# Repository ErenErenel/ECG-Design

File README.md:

# ECG Instrumentation & Heart Rate Variability Analysis

An analog ECG front-end (instrumentation amplifier + filtering) built around the
**OP484** quad op-amp, together with a Python analysis of the acquired signal for
beat-by-beat heart rate and heart rate variability (HRV).

Developed for the **EE 495 ECG Lab** at Northwestern University.

## Analog Front-End

A Lead-I ECG is acquired with RA and LA as the differential inputs and RL as the
right-leg reference ground. The signal chain runs on a single OP484 (four op-amps,
±5 V supply):

- **Instrumentation amplifier (3 op-amps)** — total gain ≈ 25
  - First stage (differential): G₁ = (2R₂ + R₁)/R₁ = 5, with R₂ = 20 kΩ, R₁ = 10 kΩ
  - Second stage (difference amp): G₂ = R₆/R₄ = 5, with R₆ = 100 kΩ, R₄ = 20 kΩ
- **Gain + filtering stage (4th op-amp)** — additional gain and approximate
  1–100 Hz band-limiting (high-pass + low-pass) to suppress baseline drift and
  high-frequency interference.

Bench verification with a 10 mV differential sine drove an output near 0.25 V,
confirming the ×25 instrumentation-amp gain across the 1–1000 Hz range.

## Heart Rate & HRV Analysis

A ~1-minute Lead-I recording was digitized at **fₛ = 1000 Hz** and analyzed in Python:

- **R-peak detection** — threshold-based (750 mV) with a 0.25 s refractory period and
  recovery of missed beats from abnormally long RR intervals. **72 R-peaks** detected.
- **Beat-by-beat heart rate** — computed from RR intervals (HRᵢ = 60 / RRᵢ),
  starting around 74.6 bpm.
- **HRV spectral analysis** — the mean HR is removed and an FFT-based power spectrum
  of the HR signal shows most variability at low frequencies (≤ 2 Hz, with a bump near
  ~0.18 Hz) associated with autonomic / respiratory modulation.

## Repository Structure

```
ECG-Design/
├── ECG PCB Files/          KiCad schematic, layout, and project for the ECG board
│   ├── ECG.kicad_sch
│   ├── ECG.kicad_pcb
│   └── ECG.kicad_pro
├── EE495 ECG Lab.pdf       Lab report: instrumentation amp design + ECG acquisition
└── Heart Rate Variability Analysis.pdf
                            HR and HRV analysis of the recorded ECG
```

Open `ECG PCB Files/ECG.kicad_pro` in **KiCad 7+** to view the schematic and board.

## License

Released under the [MIT License](LICENSE).

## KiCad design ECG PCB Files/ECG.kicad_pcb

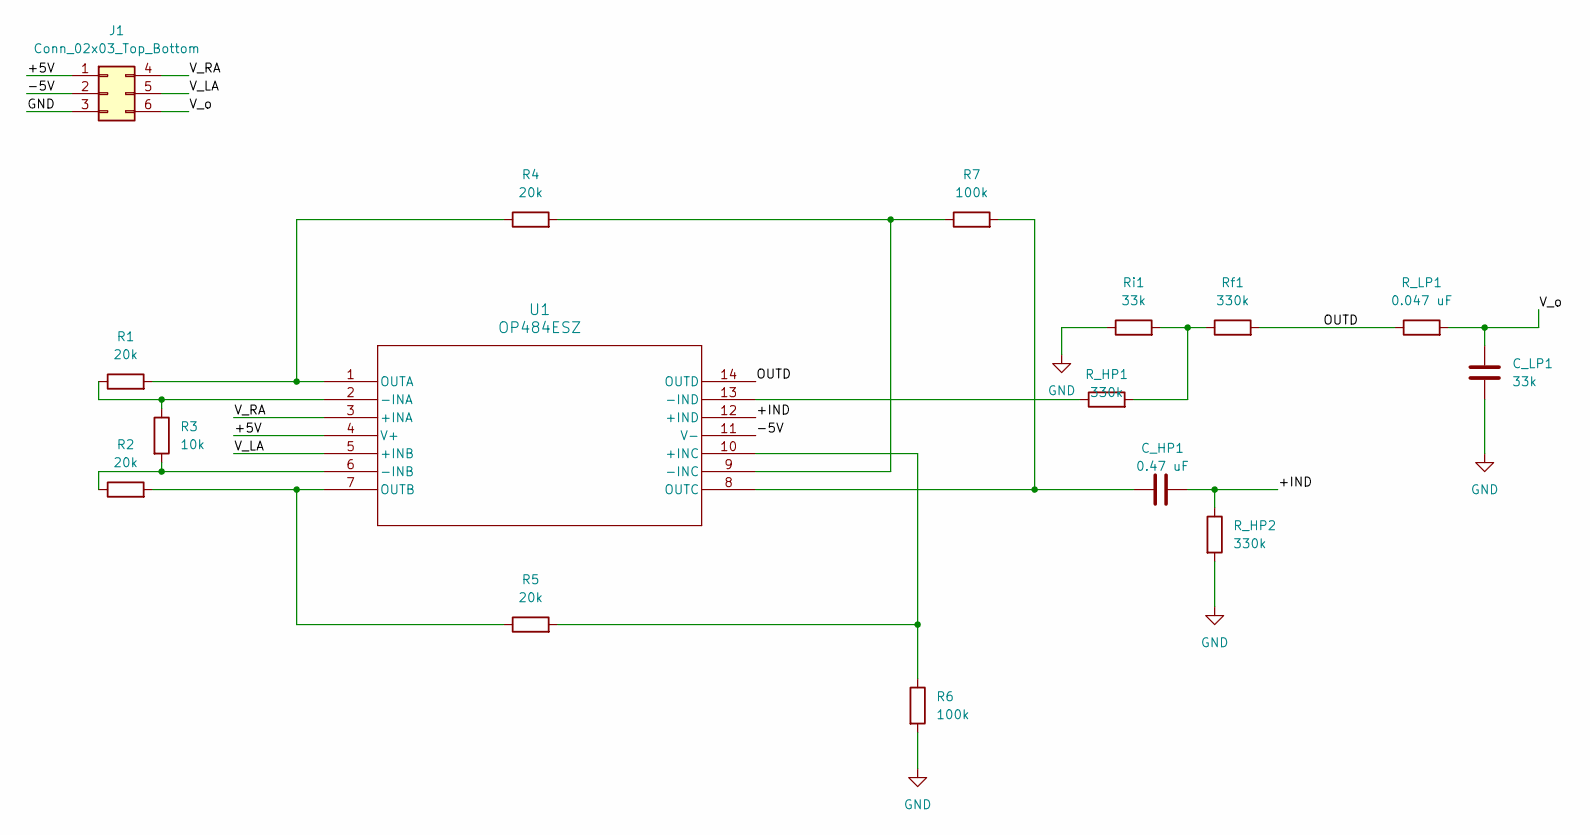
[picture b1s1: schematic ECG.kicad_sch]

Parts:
C_HP1: 0.47 uF; C_0805_2012Metric
C_LP1: 33k; C_0805_2012Metric
J1: Conn_02x03_Top_Bottom; PinHeader_2x03_P2.54mm_Vertical
R1, R2, R4, R5: 20k; R_0805_2012Metric
R3: 10k; R_0805_2012Metric
R6, R7: 100k; R_0805_2012Metric
R_HP1, R_HP2: 330k; R_0805_2012Metric
R_LP1: 0.047 uF; R_0805_2012Metric
Rf1: 330k; R_0805_2012Metric
Ri1: 33k; R_0805_2012Metric
U1: OP484ESZ; R_14_ADI

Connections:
/+5V: J1.1, U1.4 (V+)
/+IND: C_HP1.2, R_HP2.1, U1.12 (+IND)
/-5V: J1.2, U1.11 (V-)
/OUTD: R_LP1.1, Rf1.2, U1.14 (OUTD)
/V_LA: J1.5, U1.5 (+INB)
/V_RA: J1.4, U1.3 (+INA)
/V_o: C_LP1.1, J1.6, R_LP1.2
GND: C_LP1.2, J1.3, R6.2, R_HP2.2, Ri1.1
unnamed: R_HP1.2, Rf1.1, Ri1.2
unnamed: R5.2, R6.1, U1.10 (+INC)
unnamed: R1.1, R3.1, U1.2 (-INA)
unnamed: R2.1, R3.2, U1.6 (-INB)
unnamed: R4.2, R7.1, U1.9 (-INC)
unnamed: R_HP1.1, U1.13 (-IND)
unnamed: R1.2, R4.1, U1.1 (OUTA)
unnamed: R2.2, R5.1, U1.7 (OUTB)
unnamed: C_HP1.1, R7.2, U1.8 (OUTC)

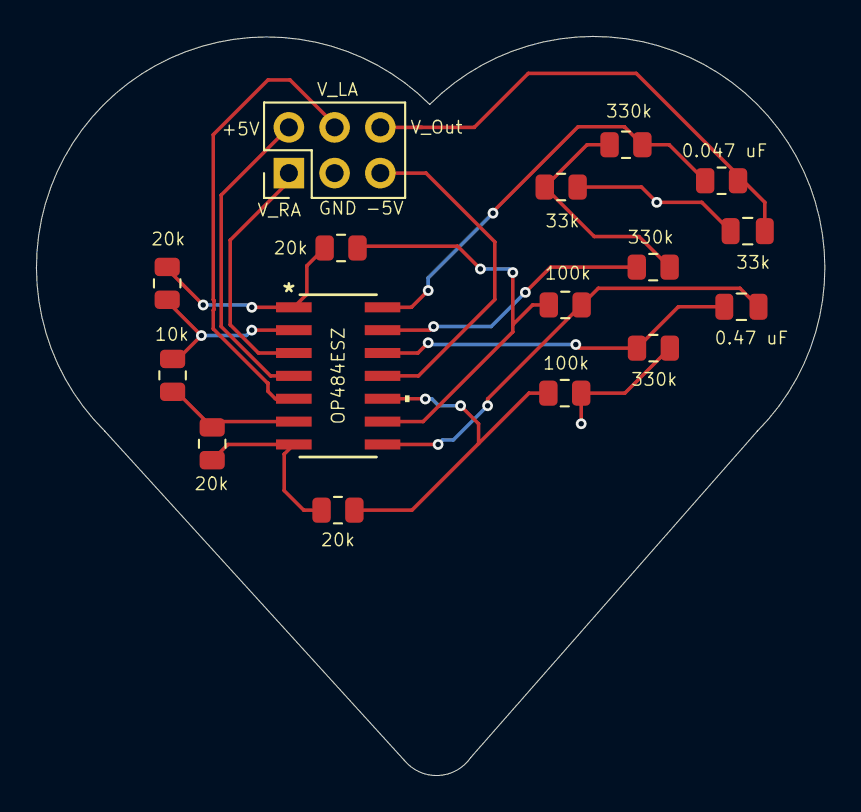
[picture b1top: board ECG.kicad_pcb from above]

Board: 2 copper layers, 43.8 x 41.1 mm, 16 parts (0 on the bottom side), 17 nets.

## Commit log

2026-03-03 ecg report + design files
2026-06-25 Add .gitignore, remove generated KiCad files and .DS_Store from tracking
    Untrack fp-info-cache, .kicad_prl, KiCad auto-backups, and .DS_Store.
2026-06-25 Write detailed README covering analog front-end and HRV analysis
